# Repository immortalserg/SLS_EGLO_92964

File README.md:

# SLS zigbee шлюз в корпус ночника EGLO 92964

плата для модификации ночника в SLS шлюз. 

Zigbee UART RX: 22

Zigbee UART TX: 23

Service Button Pin: 33 PullUp

Number addressable leds: 4

Led Red (or addr): 4

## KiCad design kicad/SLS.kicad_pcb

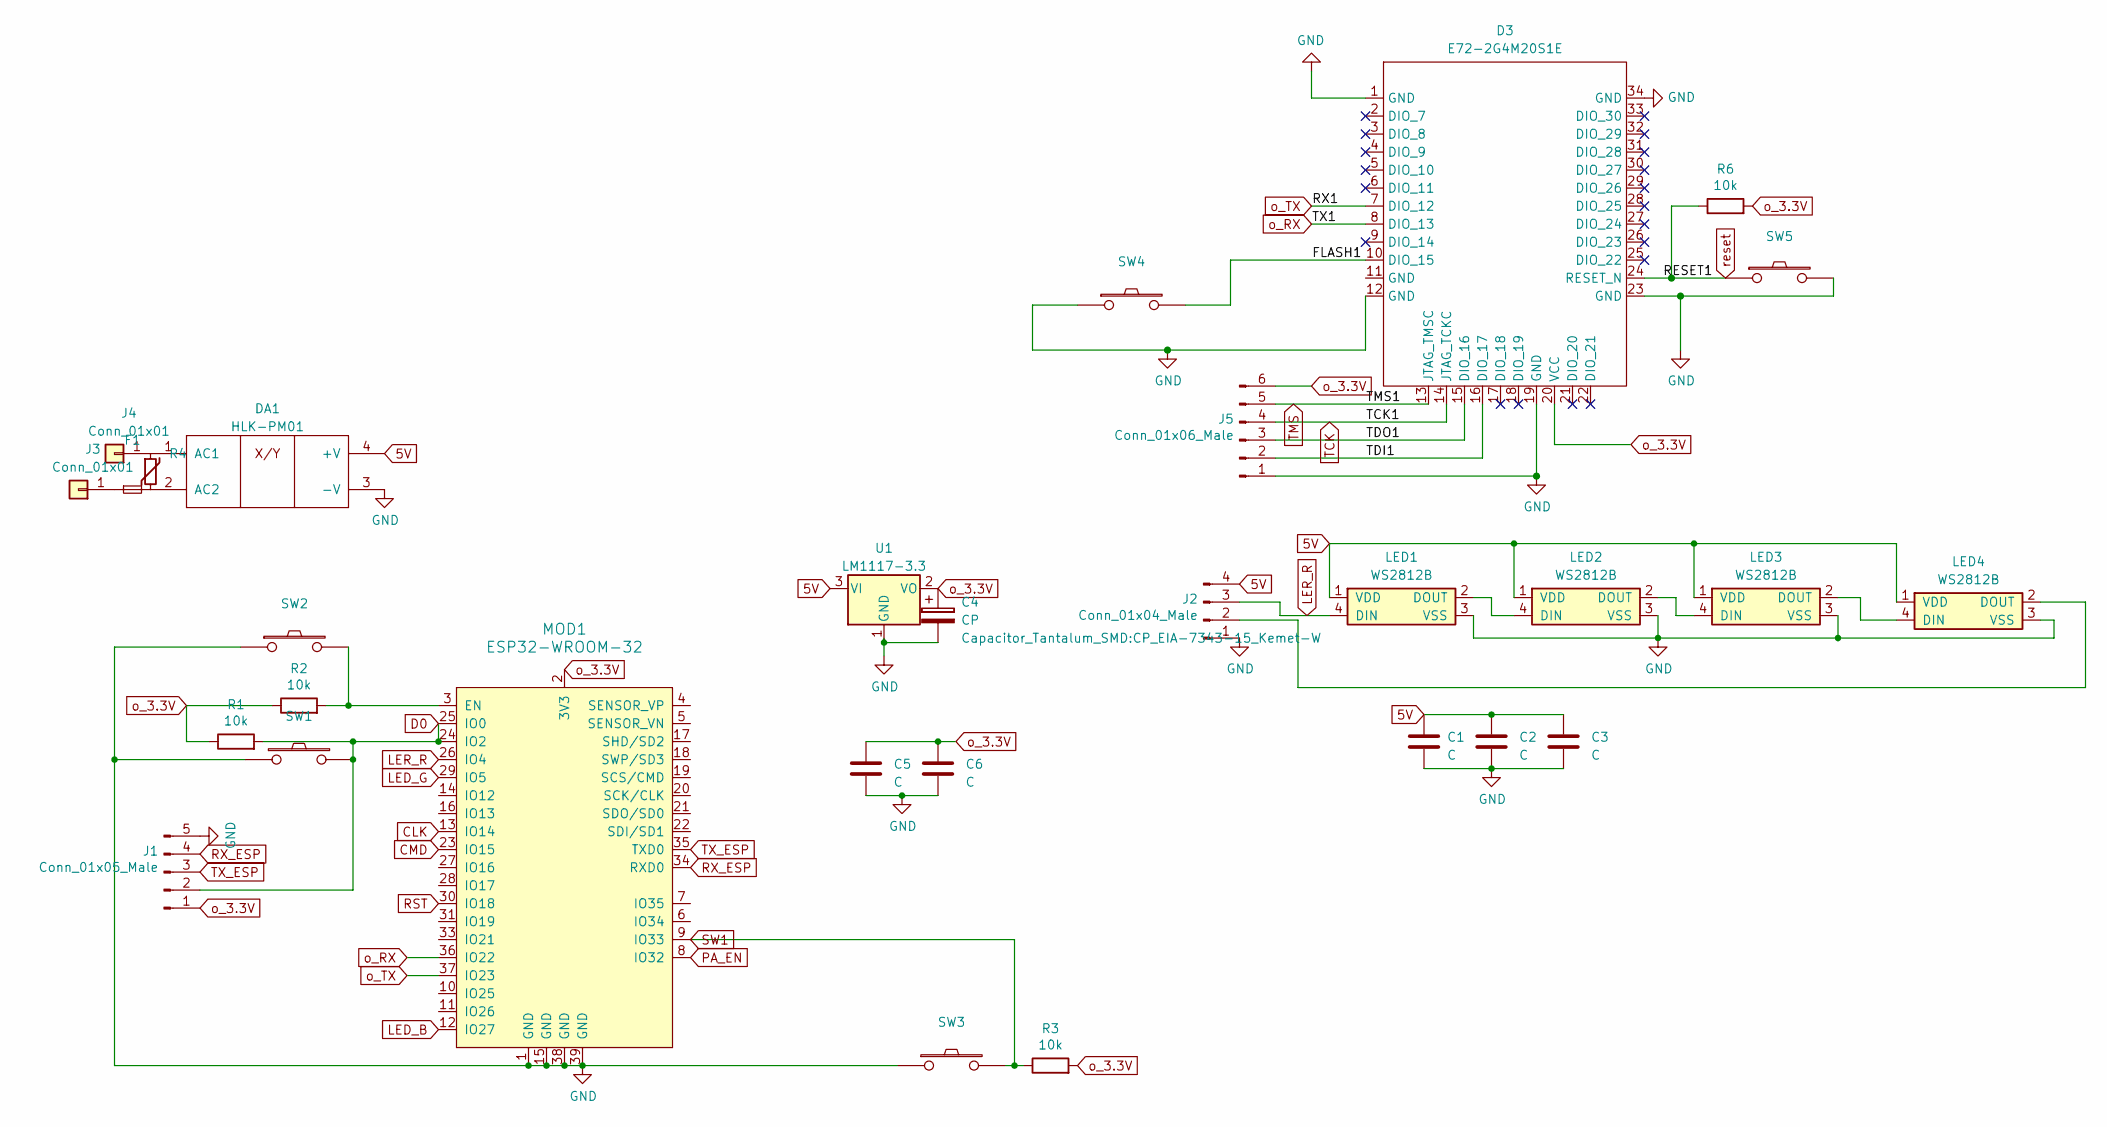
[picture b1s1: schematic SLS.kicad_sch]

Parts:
C1, C2, C3, C5, C6: C; C_1206_3216Metric
C4: CP; CP_EIA-7343-15_Kemet-W
D3: E72-2G4M20S1E
DA1: HLK-PM01; HLK-PM0x
F1: F_Small; R_Axial_DIN0207_L6.3mm_D2.5mm_P7.62mm_Horizontal
J1: Conn_01x05_Male; PinHeader_1x05_P2.54mm_Vertical
J2: Conn_01x04_Male; PinHeader_1x04_P2.54mm_Vertical
J3, J4: Conn_01x01; PinHeader_1x01_P2.54mm_Vertical
J5: Conn_01x06_Male; PinHeader_1x06_P2.54mm_Vertical
LED1, LED2, LED3, LED4: WS2812B; LED_WS2812B_PLCC4_5.0x5.0mm_P3.2mm
MOD1: ESP32-WROOM-32; ESP32-WROOM-32D; MPN ESP32-WROOM-32; Digi-Key_PN 1904-1010-1-ND
R1, R2, R3, R6: 10k; R_1206_3216Metric
R4: VARISTOR; RV_Disc_D12mm_W3.9mm_P7.5mm
SW1, SW2, SW3, SW4, SW5: SW_PUSH; SW_SPST_CK_RS282G05A3
U1: LM1117-3.3; SOT-223-3_TabPin2

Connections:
5V: C1.1, C2.1, C3.1, DA1.4 (+V), J2.4, LED1.1 (VDD), LED2.1 (VDD), LED3.1 (VDD), LED4.1 (VDD), U1.3 (VI)
/FLASH1: D3.10 (DIO_15), SW4.2
/TDI1: D3.16 (DIO_17), J5.2
/TDO1: D3.15 (DIO_16), J5.3
CLK: MOD1.13 (IO14)
CMD: MOD1.23 (IO15)
D0: J1.2, MOD1.24 (IO2), MOD1.25 (IO0), R1.2, SW1.2
GND: C1.2, C2.2, C3.2, C4.2, C5.2, C6.2, D3.1 (GND), D3.12 (GND), D3.19 (GND), D3.23 (GND), D3.34 (GND), DA1.3 (-V), J1.5, J2.1, J5.1, LED1.3 (VSS), LED2.3 (VSS), LED3.3 (VSS), LED4.3 (VSS), MOD1.1 (GND), MOD1.15 (GND), MOD1.38 (GND), MOD1.39 (GND), SW1.1, SW2.1, SW3.1, SW4.1, SW5.2, U1.1 (GND)
LED_B: MOD1.12 (IO27)
LED_G: MOD1.29 (IO5)
LER_R: J2.3, LED1.4 (DIN), MOD1.26 (IO4)
unnamed: DA1.1 (AC1), J4.1, R4.1
unnamed: DA1.2 (AC2), F1.2, R4.2
unnamed: F1.1, J3.1
unnamed: J2.2, LED4.2 (DOUT)
unnamed: LED1.2 (DOUT), LED2.4 (DIN)
unnamed: LED2.2 (DOUT), LED3.4 (DIN)
unnamed: LED3.2 (DOUT), LED4.4 (DIN)
unnamed: MOD1.3 (EN), R2.2, SW2.2
PA_EN: MOD1.8 (IO32)
RST: MOD1.30 (IO18)
RX_ESP: J1.4, MOD1.34 (RXD0)
SW1: MOD1.9 (IO33), R3.1, SW3.2
TCK: D3.14 (JTAG_TCKC), J5.4
TMS: D3.13 (JTAG_TMSC), J5.5
TX_ESP: J1.3, MOD1.35 (TXD0)
o_3.3V: C4.1, C5.1, C6.1, D3.20 (VCC), J1.1, J5.6, MOD1.2 (3V3), R1.1, R2.1, R3.2, R6.2, U1.2 (VO)
o_RX: D3.8 (DIO_13), MOD1.36 (IO22)
o_TX: D3.7 (DIO_12), MOD1.37 (IO23)
reset: D3.24 (RESET_N), R6.1, SW5.1

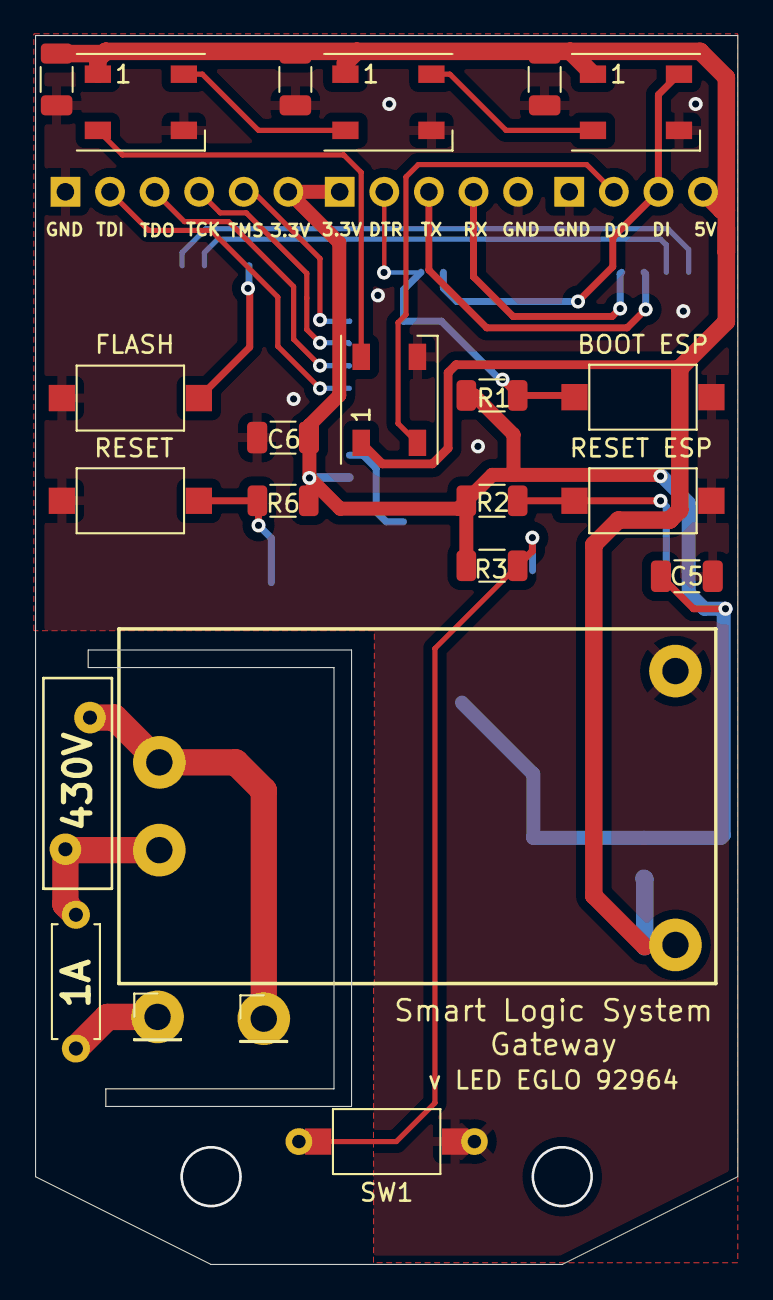
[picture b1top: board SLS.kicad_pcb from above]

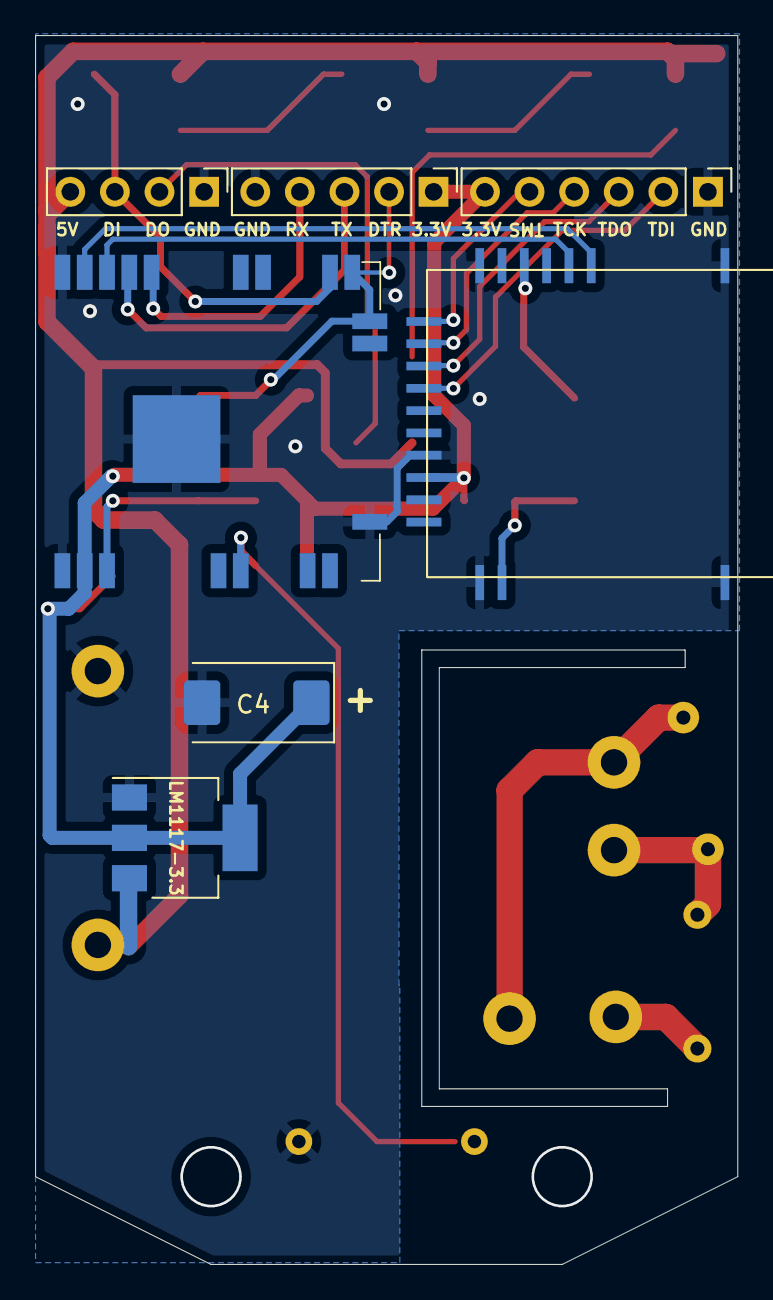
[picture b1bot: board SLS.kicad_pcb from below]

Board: 2 copper layers, 40.0 x 70.0 mm, 30 parts (7 on the bottom side), 24 nets.

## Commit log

2024-01-08 Create 1
2025-02-23 Rename ui.lua to ui.html
